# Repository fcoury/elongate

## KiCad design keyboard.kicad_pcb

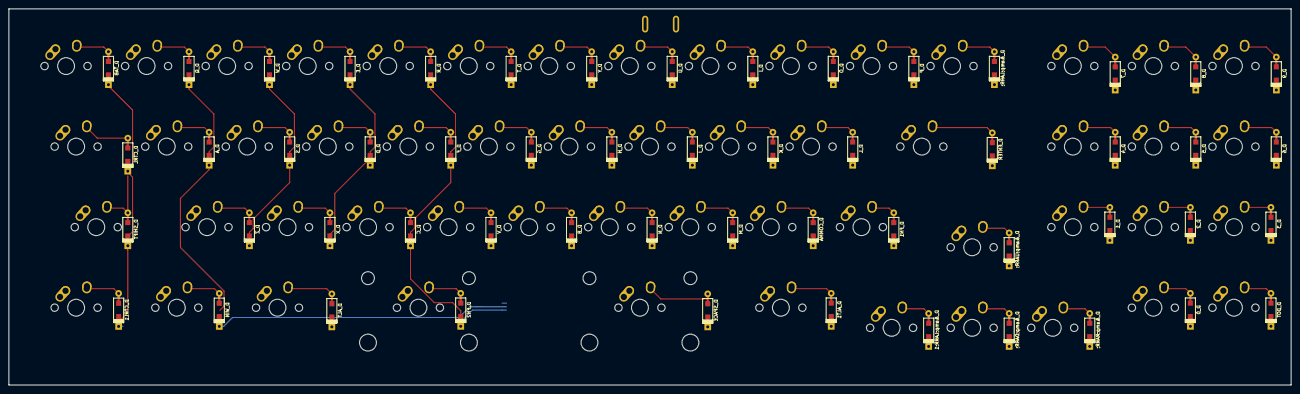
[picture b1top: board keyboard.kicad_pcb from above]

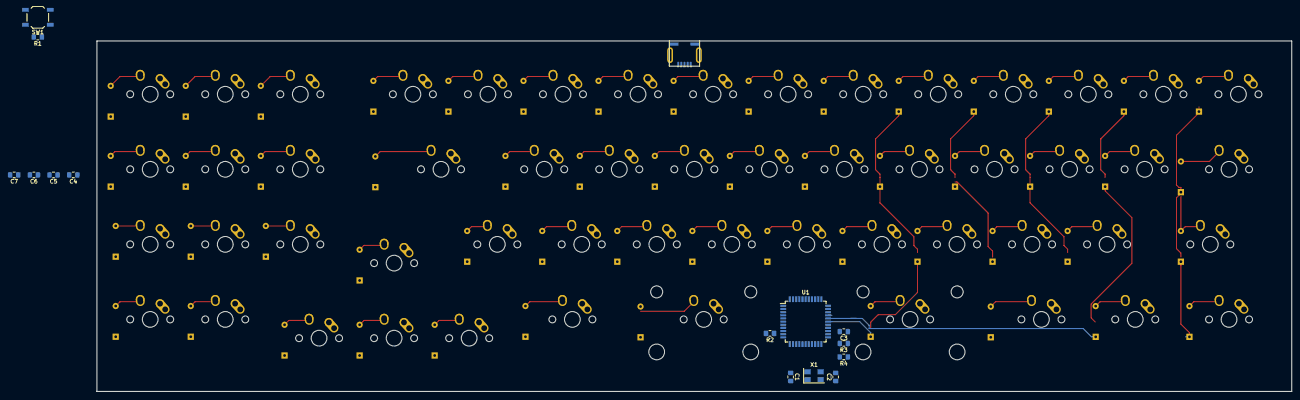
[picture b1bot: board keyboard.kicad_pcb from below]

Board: 2 copper layers, 303.3 x 89.0 mm, 123 parts (15 on the bottom side), 81 nets.

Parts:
C1, C2, C3, C4, C5, C6, C7: 22pF; C_0805_2012Metric_Pad1.15x1.40mm_HandSolder
D_0, D_1, D_2, D_3, D_4, D_5, D_6, D_7, D_8, D_9: D; D_SOD123_axial
D_&amp;DARR;: D; D_SOD123_axial
D_&amp;LARR;, D_&amp;LARR;1: D; D_SOD123_axial
D_&amp;RARR;: D; D_SOD123_axial
D_&amp;UARR;: D; D_SOD123_axial
D_A: D; D_SOD123_axial
D_ALT, D_ALT1: D; D_SOD123_axial
D_B: D; D_SOD123_axial
D_C: D; D_SOD123_axial
D_COMMA: D; D_SOD123_axial
D_CTRL, D_CTRL1: D; D_SOD123_axial
D_D: D; D_SOD123_axial
D_DOT: D; D_SOD123_axial
D_E: D; D_SOD123_axial
D_ENTER: D; D_SOD123_axial
D_F: D; D_SOD123_axial
D_FN1, D_FN2: D; D_SOD123_axial
D_G: D; D_SOD123_axial
D_H: D; D_SOD123_axial
D_I: D; D_SOD123_axial
D_J: D; D_SOD123_axial
D_K: D; D_SOD123_axial
D_L: D; D_SOD123_axial
D_M: D; D_SOD123_axial
D_N: D; D_SOD123_axial
D_O: D; D_SOD123_axial
D_P: D; D_SOD123_axial
D_Q: D; D_SOD123_axial
D_R: D; D_SOD123_axial
D_S: D; D_SOD123_axial
D_SHIFT: D; D_SOD123_axial
D_SPACE: D; D_SOD123_axial
D_T: D; D_SOD123_axial
D_TAB: D; D_SOD123_axial
D_U: D; D_SOD123_axial
D_V: D; D_SOD123_axial
D_W: D; D_SOD123_axial
D_WIN: D; D_SOD123_axial
D_X: D; D_SOD123_axial
D_Y: D; D_SOD123_axial
D_Z: D; D_SOD123_axial
K_0, K_1, K_2, K_3, K_4, K_5, K_6, K_7, K_8, K_9: KEYSW; MX-1U-NoLED
K_&amp;DARR;: KEYSW; MX-1U-NoLED
K_&amp;LARR;, K_&amp;LARR;1: KEYSW; MX-1U-NoLED
K_&amp;RARR;: KEYSW; MX-1U-NoLED
K_&amp;UARR;: KEYSW; MX-1U-NoLED
K_A: KEYSW; MX-1U-NoLED
K_ALT, K_ALT1: KEYSW; MX-1.25U-NoLED
K_B: KEYSW; MX-1U-NoLED
K_C: KEYSW; MX-1U-NoLED
K_COMMA: KEYSW; MX-1U-NoLED
K_CTRL, K_CTRL1: KEYSW; MX-1.25U-NoLED
K_D: KEYSW; MX-1U-NoLED
K_DOT: KEYSW; MX-1U-NoLED
K_E: KEYSW; MX-1U-NoLED
K_ENTER: KEYSW; MX-1.75U-NoLED
K_F: KEYSW; MX-1U-NoLED
K_FN1: KEYSW; MX-1.25U-NoLED
K_FN2: KEYSW; MX-2.25U-NoLED
K_G: KEYSW; MX-1U-NoLED
K_H: KEYSW; MX-1U-NoLED
K_I: KEYSW; MX-1U-NoLED
K_J: KEYSW; MX-1U-NoLED
K_K: KEYSW; MX-1U-NoLED
K_L: KEYSW; MX-1U-NoLED
K_M: KEYSW; MX-1U-NoLED
K_N: KEYSW; MX-1U-NoLED
K_O: KEYSW; MX-1U-NoLED
K_P: KEYSW; MX-1U-NoLED
K_Q: KEYSW; MX-1U-NoLED
K_R: KEYSW; MX-1U-NoLED
K_S: KEYSW; MX-1U-NoLED
K_SHIFT: KEYSW; MX-1.75U-NoLED
K_SPACE: KEYSW; MX-2.25U-NoLED
K_T: KEYSW; MX-1U-NoLED
K_TAB: KEYSW; MX-1U-NoLED
K_U: KEYSW; MX-1U-NoLED
K_V: KEYSW; MX-1U-NoLED
K_W: KEYSW; MX-1U-NoLED
K_WIN: KEYSW; MX-1.25U-NoLED
K_X: KEYSW; MX-1U-NoLED
K_Y: KEYSW; MX-1U-NoLED
K_Z: KEYSW; MX-1U-NoLED
R1, R2: 10k; R_0805_2012Metric_Pad1.15x1.40mm_HandSolder
R3, R4: 22u; R_0805_2012Metric_Pad1.15x1.40mm_HandSolder
SW1: SW_PUSH; SW_SPST_TL3342
U1: ATMEGA32U4; TQFP-44_10x10mm_P0.8mm
USB1: USB_mini_micro_B; USB_miniB_hirose_5S8
X1: XTAL_GND; Crystal_SMD_5032-4Pin_5.0x3.2mm

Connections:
/col0: D_CTRL.1, D_CTRL1.1, D_SHIFT.1, D_TAB.1, U1.30
/col1: D_A.1, D_Q.1, D_WIN.1, U1.29
/col2: D_S.1, D_W.1, D_Z.1, U1.27
/col3: D_ALT.1, D_D.1, D_E.1, D_X.1, U1.12
/col4: D_C.1, D_F.1, D_FN2.1, D_R.1, U1.28
/col5: D_G.1, D_T.1, D_V.1, U1.32
/col6: D_B.1, D_H.1, D_Y.1, U1.18
/col7: D_J.1, D_N.1, D_SPACE.1, D_U.1, U1.19
/col8: D_I.1, D_K.1, D_M.1, U1.20
/col9: D_ALT1.1, D_COMMA.1, D_L.1, D_O.1, U1.21
/col10: D_&amp;LARR;1.1, D_FN1.1, D_P.1, U1.25
/col11: D_&amp;DARR;.1, D_&amp;LARR;.1, D_&amp;UARR;.1, D_ENTER.1, U1.22
/col12: D_&amp;RARR;.1, U1.26
/col13: D_1.1, D_4.1, D_7.1, U1.31
/col14: D_0.1, D_2.1, D_5.1, D_8.1, U1.41
/col15: D_3.1, D_6.1, D_9.1, D_DOT.1, U1.40
GND: C1.2, C2.2, C3.2, C4.2, C5.2, C6.2, C7.2, R2.2, SW1.1, U1.5, U1.15, U1.23, USB1.5, USB1.6, X1.3
unnamed: C1.1, U1.16, X1.1
unnamed: C2.1, U1.17, X1.2
unnamed: C3.1, U1.6
unnamed: D_0.2, K_0.2
unnamed: D_1.2, K_1.2
unnamed: D_2.2, K_2.2
unnamed: D_3.2, K_3.2
unnamed: D_4.2, K_4.2
unnamed: D_5.2, K_5.2
unnamed: D_6.2, K_6.2
unnamed: D_7.2, K_7.2
unnamed: D_8.2, K_8.2
unnamed: D_9.2, K_9.2
unnamed: D_&amp;DARR;.2, K_&amp;DARR;.2
unnamed: D_&amp;LARR;1.2, K_&amp;LARR;1.2
unnamed: D_&amp;LARR;.2, K_&amp;LARR;.2
unnamed: D_&amp;RARR;.2, K_&amp;RARR;.2
unnamed: D_&amp;UARR;.2, K_&amp;UARR;.2
unnamed: D_A.2, K_A.2
unnamed: D_ALT1.2, K_ALT1.2
unnamed: D_ALT.2, K_ALT.2
unnamed: D_B.2, K_B.2
unnamed: D_C.2, K_C.2
unnamed: D_COMMA.2, K_COMMA.2
unnamed: D_CTRL1.2, K_CTRL1.2
unnamed: D_CTRL.2, K_CTRL.2
unnamed: D_D.2, K_D.2
unnamed: D_DOT.2, K_DOT.2
unnamed: D_E.2, K_E.2
unnamed: D_ENTER.2, K_ENTER.2
unnamed: D_F.2, K_F.2
unnamed: D_FN1.2, K_FN1.2
unnamed: D_FN2.2, K_FN2.2
unnamed: D_G.2, K_G.2
unnamed: D_H.2, K_H.2
unnamed: D_I.2, K_I.2
unnamed: D_J.2, K_J.2
unnamed: D_K.2, K_K.2
unnamed: D_L.2, K_L.2
unnamed: D_M.2, K_M.2
unnamed: D_N.2, K_N.2
unnamed: D_O.2, K_O.2
unnamed: D_P.2, K_P.2
unnamed: D_Q.2, K_Q.2
unnamed: D_R.2, K_R.2
unnamed: D_S.2, K_S.2
unnamed: D_SHIFT.2, K_SHIFT.2
unnamed: D_SPACE.2, K_SPACE.2
unnamed: D_T.2, K_T.2
unnamed: D_TAB.2, K_TAB.2
unnamed: D_U.2, K_U.2
unnamed: D_V.2, K_V.2
unnamed: D_W.2, K_W.2
unnamed: D_WIN.2, K_WIN.2
unnamed: D_X.2, K_X.2
unnamed: D_Y.2, K_Y.2
unnamed: D_Z.2, K_Z.2
unnamed: R1.1, SW1.2, U1.13
unnamed: R2.1, U1.33
unnamed: R3.1, U1.3
unnamed: R4.1, U1.4
unnamed: R3.2, USB1.2
unnamed: R4.2, USB1.3
VCC: C4.1, C5.1, C6.1, C7.1, R1.2, U1.2, U1.14, U1.24, USB1.1

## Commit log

2019-04-03 chore: initial commit
2019-04-04 feat: completed PCB
